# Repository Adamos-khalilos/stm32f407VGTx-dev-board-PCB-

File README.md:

# STM32F407VGTx Dev Board

A custom STM32F407VGTx development board featuring USB-C power/data, a microSD card slot, SWD debugging, a wake-up button, RGB status LEDs, and a clean regulated power supply. Designed entirely in KiCad.

<!-- Replace with your 3D render or PCB photo -->

## Features

- **MCU**: STM32F407VGTx (ARM Cortex-M4, up to 168 MHz)
- **USB**: USB-C receptacle (USB 2.0) with ESD protection (USBLC6-2P6) and BOOT0 select button
- **Power**: 5V → 3.3V regulation via LP5907MFX-3.3 LDO, decoupled with a full capacitor array on VDD/VDDA
- **Storage**: microSD card socket with dedicated pull-ups on DAT0–3/CMD/CLK and card-detect pins
- **Debug**: SWD header (Tag-Connect TC2030-NL footprint) — SWDIO, SWCLK, nRST, VCC, GND
- **Reset circuit**: Dedicated reset button with debounce and PWR_FLAG supervision
- **Wake-up circuit**: Dedicated WKUP button on a pull-down
- **Clock**: 8 MHz external crystal (HSE) with 27pF load capacitors
- **Status LEDs**: RED, GREEN, BLUE, ORANGE user LEDs (330 Ω current-limiting resistors)
- **Expansion**: Two 2×25 GPIO headers (J4 "right side", J5 "left side") breaking out nearly all MCU pins, plus 3V3/5V/GND rails

## Power Architecture

| Stage | Description |
|-------|-------------|
| USB-C VBUS (5V) | Main input power from USB-C connector (J1) |
| LP5907MFX-3.3 (U2) | Linear regulator, 5V → 3.3V |
| VDD / VDDA decoupling | Array of 100 nF capacitors + bulk 4.7 µF on the MCU supply rails |
| High-frequency filtering | Ferrite bead (FB1) + local 100 pF / 4.7 µF caps close to VREF/VDDA for clean ADC reference |

## USB-C Interface (J1)

- USB 2.0 receptacle, D+/D− routed to PA11/PA12
- ESD protection via USBLC6-2P6 (U1)
- BOOT0 select button (SW1) with pull resistors for entering system bootloader mode

## microSD Card Interface (J2)

| Signal | Description |
|--------|-------------|
| DAT0–DAT3 | SDIO data lines (10 kΩ pull-ups) |
| CLK (SDIO_CLK) | SDIO clock |
| CMD (SDIO_CMD) | SDIO command line (10 kΩ pull-up) |
| SD_DETECT / DET_A / DET_B | Card presence detection |
| SHIELD (SH) | Connector shield, tied to GND |

## SWD Debug Header (J3 — Tag-Connect TC2030-NL)

| Signal | Description |
|--------|-------------|
| VCC | +3V3 |
| SWDIO | Serial wire data |
| SWCLK | Serial wire clock |
| nRST | Reset |
| GND | Ground |

## Reset Circuit

Push-button reset with RC debounce, PWR_FLAG supervision, and a jumper (JP2) for optional external reset control.

## Wake-Up Circuit

Dedicated button (SW2) on the WKUP pin, pulled down through a 10 kΩ resistor.

## User LEDs

| LED | Color | Driver Resistor |
|-----|-------|------------------|
| D2 | Red | R9 (330 Ω) |
| D3 | Green | R10 (330 Ω) |
| D4 | Blue | R8 (330 Ω) |
| D5 | Orange | R11 (330 Ω) |

## Clock

8 MHz crystal (Y1) on HSE, with 27 pF load capacitors (C2, C3).

## GPIO Expansion Headers (J4 / J5)

Two 2×25 (50-pin) headers break out the majority of the STM32F407's GPIO ports (PA, PB, PC, PD, PE), along with GND, +3V3 and +5V rails on both headers for powering external modules.

> For the exact pin-by-pin mapping, refer to `stm32.kicad_sch` (sheet "Connector Headers") or export a netlist/pin table from KiCad — this avoids transcription errors from a schematic screenshot.

## Repository Structure
.
├── stm32.kicad_pro # KiCad project file
├── stm32.kicad_sch # Schematic
├── stm32.kicad_pcb # PCB layout
├── fp-lib-table # Footprint library table
├── Library.pretty/ # Local custom footprints
└── README.md

## Getting Started

1. Clone this repository
2. Open `stm32.kicad_pro` in [KiCad](https://www.kicad.org/) (v7 or later recommended)
3. Review the schematic (`stm32.kicad_sch`) and PCB layout (`stm32.kicad_pcb`)
4. Run DRC (Design Rules Check) before ordering fabrication
5. Generate Gerbers / fabrication files when ready to manufacture

## License

This project is licensed under the MIT License — see [LICENSE](LICENSE) for details.

## Author

Designed by **Khalil Adem**

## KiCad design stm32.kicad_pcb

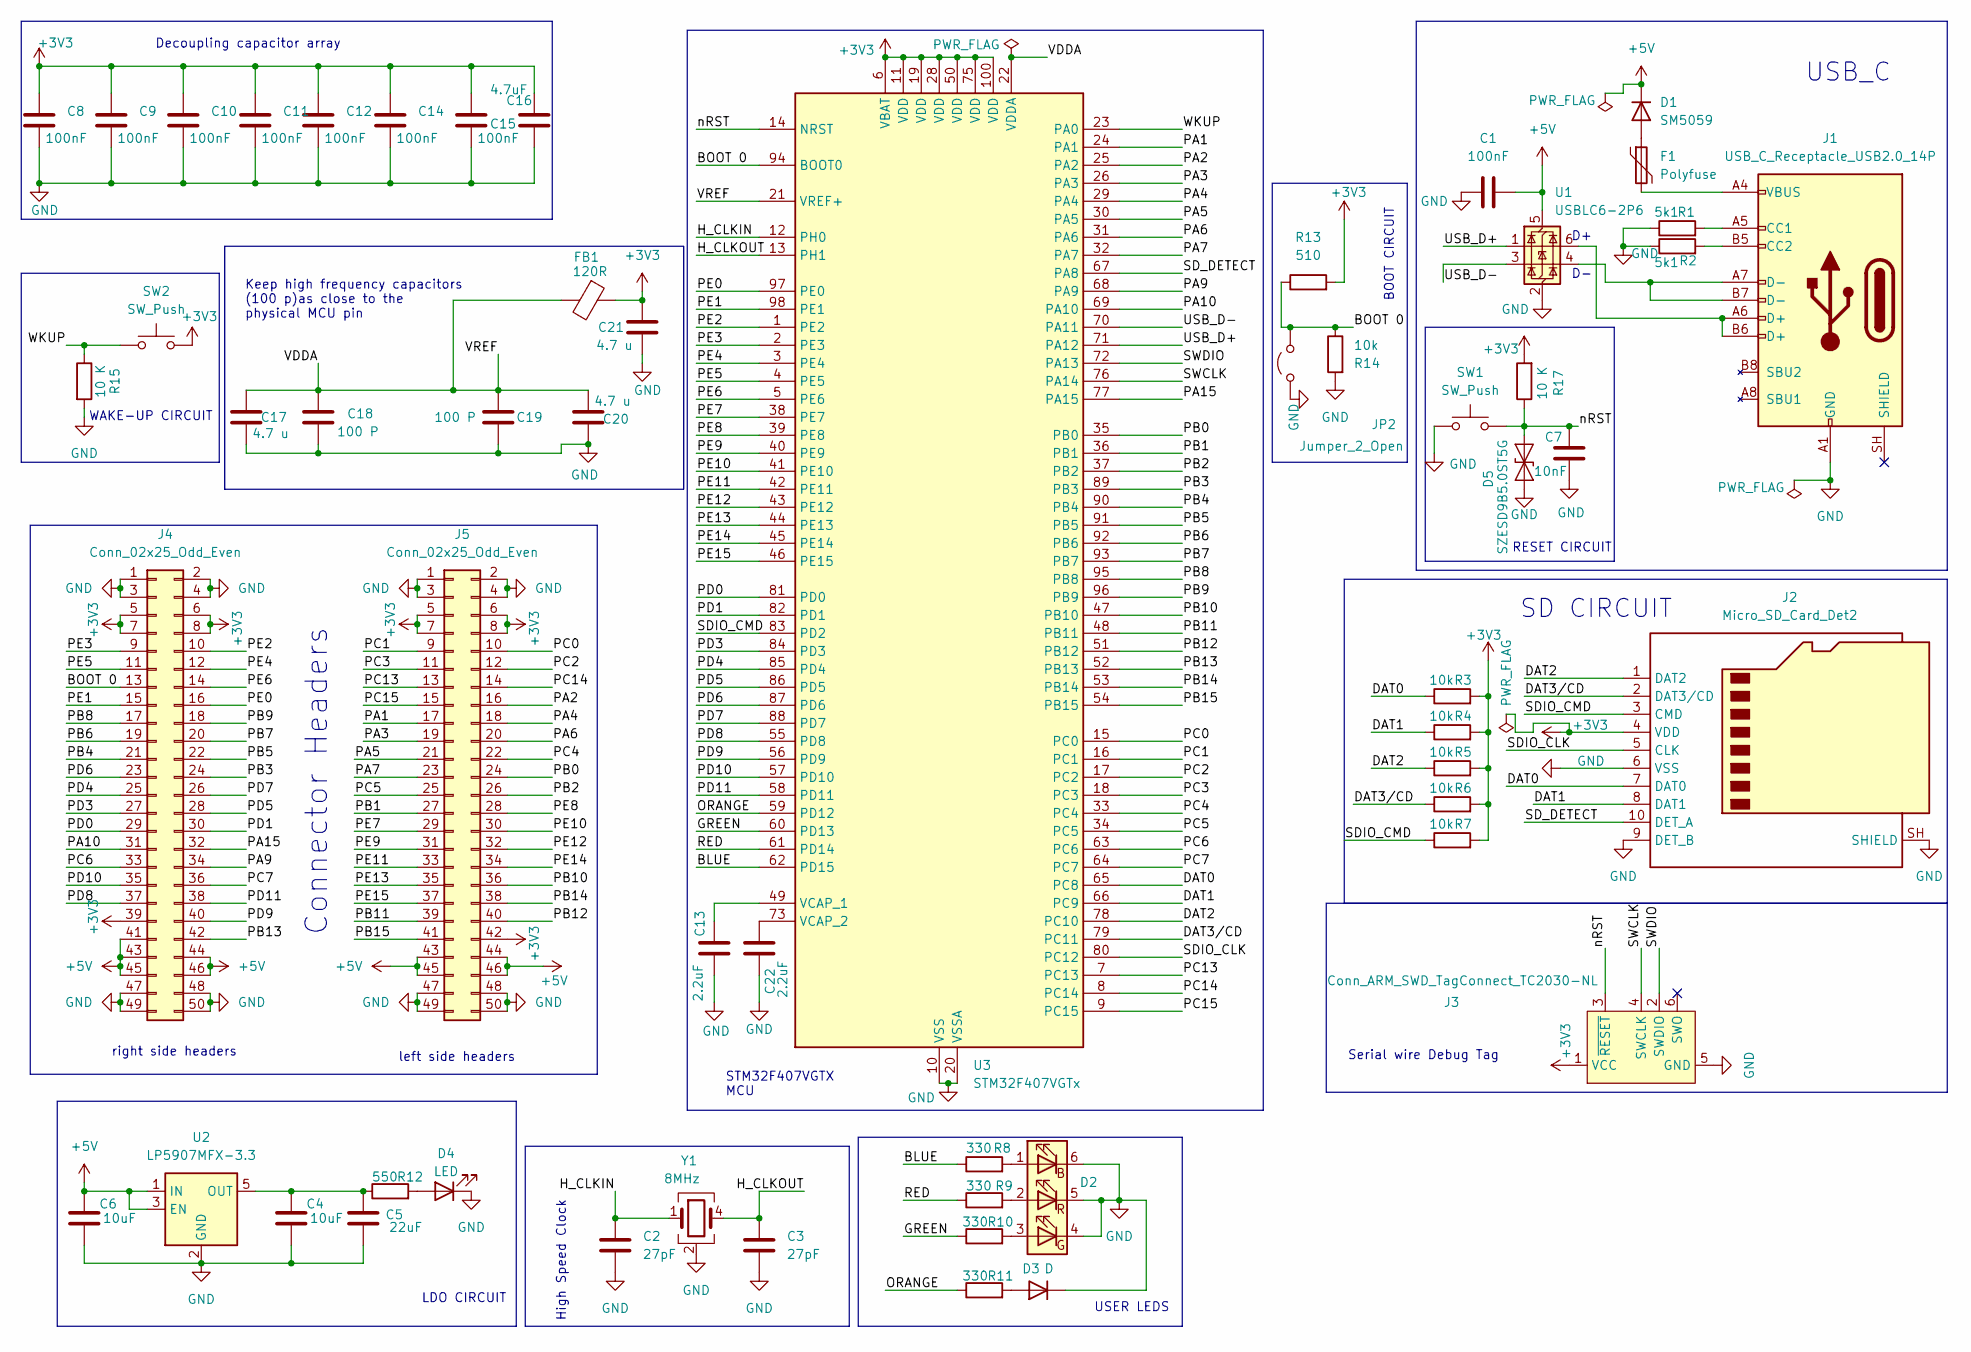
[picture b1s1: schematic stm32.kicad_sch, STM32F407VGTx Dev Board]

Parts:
C1, C8, C9, C10, C11, C12, C14, C15: 100nF; C_0603_1608Metric
C2, C3: 27pF; C_0603_1608Metric
C4, C6: 10uF; C_0805_2012Metric
C5: 22uF; C_0805_2012Metric
C7: 10nF; C_0603_1608Metric
C13, C22: 2.2uF; C_0603_1608Metric
C16: 4.7uF; C_0805_2012Metric
C17, C20, C21: 4.7 u; C_0805_2012Metric
C18, C19: 100 P; C_0603_1608Metric
D1: SM5059; D_SOD-923
D2: SMLVN6RGB; LED_ROHM_SMLVN6
D3: D; LED_0603_1608Metric
D4: LED; LED_0603_1608Metric
D5: SZESD9B5.0ST5G; D_SOD-923
F1: Polyfuse; Fuse_1206_3216Metric
FB1: 120R; L_0603_1608Metric
J1: USB_C_Receptacle_USB2.0_14P; USB_C_Receptacle_GCT_USB4105-xx-A_16P_TopMnt_Horizontal
J2: Micro_SD_Card_Det2; microSD_HC_Hirose_DM3AT-SF-PEJM5
J3: Conn_ARM_SWD_TagConnect_TC2030-NL; Tag-Connect_TC2030-IDC-NL_2x03_P1.27mm_Vertical
J4, J5: Conn_02x25_Odd_Even; PinHeader_2x25_P2.54mm_Vertical
JP2: Jumper_2_Open; SolderJumper-2_P1.3mm_Open_TrianglePad1.0x1.5mm
R1, R2: 5k1; R_0603_1608Metric
R3, R4, R5, R6, R7, R14: 10k; R_0603_1608Metric
R8, R9, R10, R11: 330; R_0603_1608Metric
R12: 550; R_0603_1608Metric
R13: 510; R_0603_1608Metric
R15, R17: 10 K; R_0603_1608Metric
SW1, SW2: SW_Push; SW_SPST_B3U-1000P
U1: USBLC6-2P6; SOT-23-6
U2: LP5907MFX-3.3; SOT-23-5
U3: STM32F407VGTx; LQFP-100_14x14mm_P0.5mm
Y1: 8MHz; Crystal_HC49-4H_Vertical

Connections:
+3V3: C8.1, C9.1, C10.1, C11.1, C12.1, C14.1, C15.1, C16.1, C21.1, FB1.1, J2.4 (VDD), J3.1 (VCC), J4.5, J4.6, J4.7, J4.8, J4.39, J5.5, J5.6, J5.7, J5.8, J5.42, R3.2, R4.2, R5.2, R6.2, R7.2, R13.2, R17.2, SW2.2, U3.6 (VBAT), U3.11 (VDD), U3.19 (VDD), U3.28 (VDD), U3.50 (VDD), U3.75 (VDD), U3.100 (VDD)
+5V: C1.2, C6.1, D1.1 (K), J4.41, J4.43, J4.44, J4.45, J4.46, J5.43, J5.44, J5.45, J5.46, U1.5 (VBUS), U2.1 (IN), U2.3 (EN)
/BLUE: R8.1, U3.62 (PD15)
/BOOT 0: J4.13, JP2.2 (B), R13.1, R14.1, U3.94 (BOOT0)
/DAT0: J2.7 (DAT0), R3.1, U3.65 (PC8)
/DAT1: J2.8 (DAT1), R4.1, U3.66 (PC9)
/DAT2: J2.1 (DAT2), R5.1, U3.78 (PC10)
/DAT3/CD: J2.2 (DAT3/CD), R6.1, U3.79 (PC11)
/GREEN: R10.1, U3.60 (PD13)
/H_CLKIN: C2.1, U3.12 (PH0), Y1.1
/H_CLKOUT: C3.1, U3.13 (PH1), Y1.4
/ORANGE: R11.1, U3.59 (PD12)
/PA1: J5.17, U3.24 (PA1)
/PA2: J5.16, U3.25 (PA2)
/PA3: J5.19, U3.26 (PA3)
/PA4: J5.18, U3.29 (PA4)
/PA5: J5.21, U3.30 (PA5)
/PA6: J5.20, U3.31 (PA6)
/PA7: J5.23, U3.32 (PA7)
/PA9: J4.34, U3.68 (PA9)
/PA10: J4.31, U3.69 (PA10)
/PA15: J4.32, U3.77 (PA15)
/PB0: J5.24, U3.35 (PB0)
/PB1: J5.27, U3.36 (PB1)
/PB2: J5.26, U3.37 (PB2)
/PB3: J4.24, U3.89 (PB3)
/PB4: J4.21, U3.90 (PB4)
/PB5: J4.22, U3.91 (PB5)
/PB6: J4.19, U3.92 (PB6)
/PB7: J4.20, U3.93 (PB7)
/PB8: J4.17, U3.95 (PB8)
/PB9: J4.18, U3.96 (PB9)
/PB10: J5.36, U3.47 (PB10)
/PB11: J5.39, U3.48 (PB11)
/PB12: J5.40, U3.51 (PB12)
/PB13: J4.42, U3.52 (PB13)
/PB14: J5.38, U3.53 (PB14)
/PB15: J5.41, U3.54 (PB15)
/PC0: J5.10, U3.15 (PC0)
/PC1: J5.9, U3.16 (PC1)
/PC2: J5.12, U3.17 (PC2)
/PC3: J5.11, U3.18 (PC3)
/PC4: J5.22, U3.33 (PC4)
/PC5: J5.25, U3.34 (PC5)
/PC6: J4.33, U3.63 (PC6)
/PC7: J4.36, U3.64 (PC7)
/PC13: J5.13, U3.7 (PC13)
/PC14: J5.14, U3.8 (PC14)
/PC15: J5.15, U3.9 (PC15)
/PD0: J4.29, U3.81 (PD0)
/PD1: J4.30, U3.82 (PD1)
/PD3: J4.27, U3.84 (PD3)
/PD4: J4.25, U3.85 (PD4)
/PD5: J4.28, U3.86 (PD5)
/PD6: J4.23, U3.87 (PD6)
/PD7: J4.26, U3.88 (PD7)
/PD8: J4.37, U3.55 (PD8)
/PD9: J4.40, U3.56 (PD9)
/PD10: J4.35, U3.57 (PD10)
/PD11: J4.38, U3.58 (PD11)
/PE0: J4.16, U3.97 (PE0)
/PE1: J4.15, U3.98 (PE1)
/PE2: J4.10, U3.1 (PE2)
/PE3: J4.9, U3.2 (PE3)
/PE4: J4.12, U3.3 (PE4)
/PE5: J4.11, U3.4 (PE5)
/PE6: J4.14, U3.5 (PE6)
/PE7: J5.29, U3.38 (PE7)
/PE8: J5.28, U3.39 (PE8)
/PE9: J5.31, U3.40 (PE9)
/PE10: J5.30, U3.41 (PE10)
/PE11: J5.33, U3.42 (PE11)
/PE12: J5.32, U3.43 (PE12)
/PE13: J5.35, U3.44 (PE13)
/PE14: J5.34, U3.45 (PE14)
/PE15: J5.37, U3.46 (PE15)
/RED: R9.1, U3.61 (PD14)
/SDIO_CLK: J2.5 (CLK), U3.80 (PC12)
/SDIO_CMD: J2.3 (CMD), R7.1, U3.83 (PD2)
/SD_DETECT: J2.10 (DET_A), U3.67 (PA8)
/SWCLK: J3.4 (SWCLK), U3.76 (PA14)
/SWDIO: J3.2 (SWDIO), U3.72 (PA13)
/USB_D+: U1.1 (I/O1), U3.71 (PA12)
/USB_D-: U1.3 (I/O2), U3.70 (PA11)
/VDDA: C17.1, C18.1, C19.1, C20.1, FB1.2, U3.21 (VREF+), U3.22 (VDDA)
/WKUP: R15.1, SW2.1, U3.23 (PA0)
/nRST: C7.1, D5.2 (A2), J3.3 (~RESET), R17.1, SW1.2, U3.14 (NRST)
GND: C1.1, C2.2, C3.2, C4.2, C5.2, C6.2, C7.2, C8.2, C9.2, C10.2, C11.2, C12.2, C13.2, C14.2, C15.2, C16.2, C17.2, C18.2, C19.2, C20.2, C21.2, C22.2, D2.4 (GK), D2.5 (RK), D2.6 (BK), D3.1 (K), D4.1 (K), D5.1 (A1), J1.A1 (GND), J1.A12 (GND), J1.B1 (GND), J1.B12 (GND), J2.6 (VSS), J2.9 (DET_B), J2.SH (SHIELD), J3.5 (GND), J4.1, J4.2, J4.3, J4.4, J4.47, J4.48, J4.49, J4.50, J5.1, J5.2, J5.3, J5.4, J5.47, J5.48, J5.49, J5.50, JP2.1 (A), R1.1, R2.1, R14.2, R15.2, SW1.1, U1.2 (GND), U2.2 (GND), U3.10 (VSS), U3.20 (VSSA), U3.27 (VSS), U3.74 (VSS), U3.99 (VSS), Y1.2 (G), Y1.3 (G)
unnamed: D1.2 (A), F1.1
unnamed: D2.1 (BA), R8.2
unnamed: D2.3 (GA), R10.2
unnamed: D2.2 (RA), R9.2
unnamed: D3.2 (A), R11.2
unnamed: D4.2 (A), R12.2
unnamed: F1.2, J1.A4 (VBUS), J1.A9 (VBUS), J1.B4 (VBUS), J1.B9 (VBUS)
unnamed: J1.A5 (CC1), R1.2
unnamed: J1.B5 (CC2), R2.2
unnamed: J1.A6 (D+), J1.B6 (D+), U1.6 (I/O1)
unnamed: J1.A7 (D-), J1.B7 (D-), U1.4 (I/O2)
unnamed: C4.1, C5.1, R12.1, U2.5 (OUT)
unnamed: C13.1, U3.49 (VCAP_1)
unnamed: C22.1, U3.73 (VCAP_2)

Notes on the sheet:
STM32F407VGTX MCU
WAKE-UP CIRCUIT
High Speed Clock
Keep high frequency capacitors (100 p)as close to the physical MCU pin
LDO CIRCUIT
SD CIRCUIT
USB_C
Decoupling capacitor array
left side headers
USER LEDS
RESET CIRCUIT
Connector Headers
right side headers
Serial wire Debug Tag
BOOT CIRCUIT

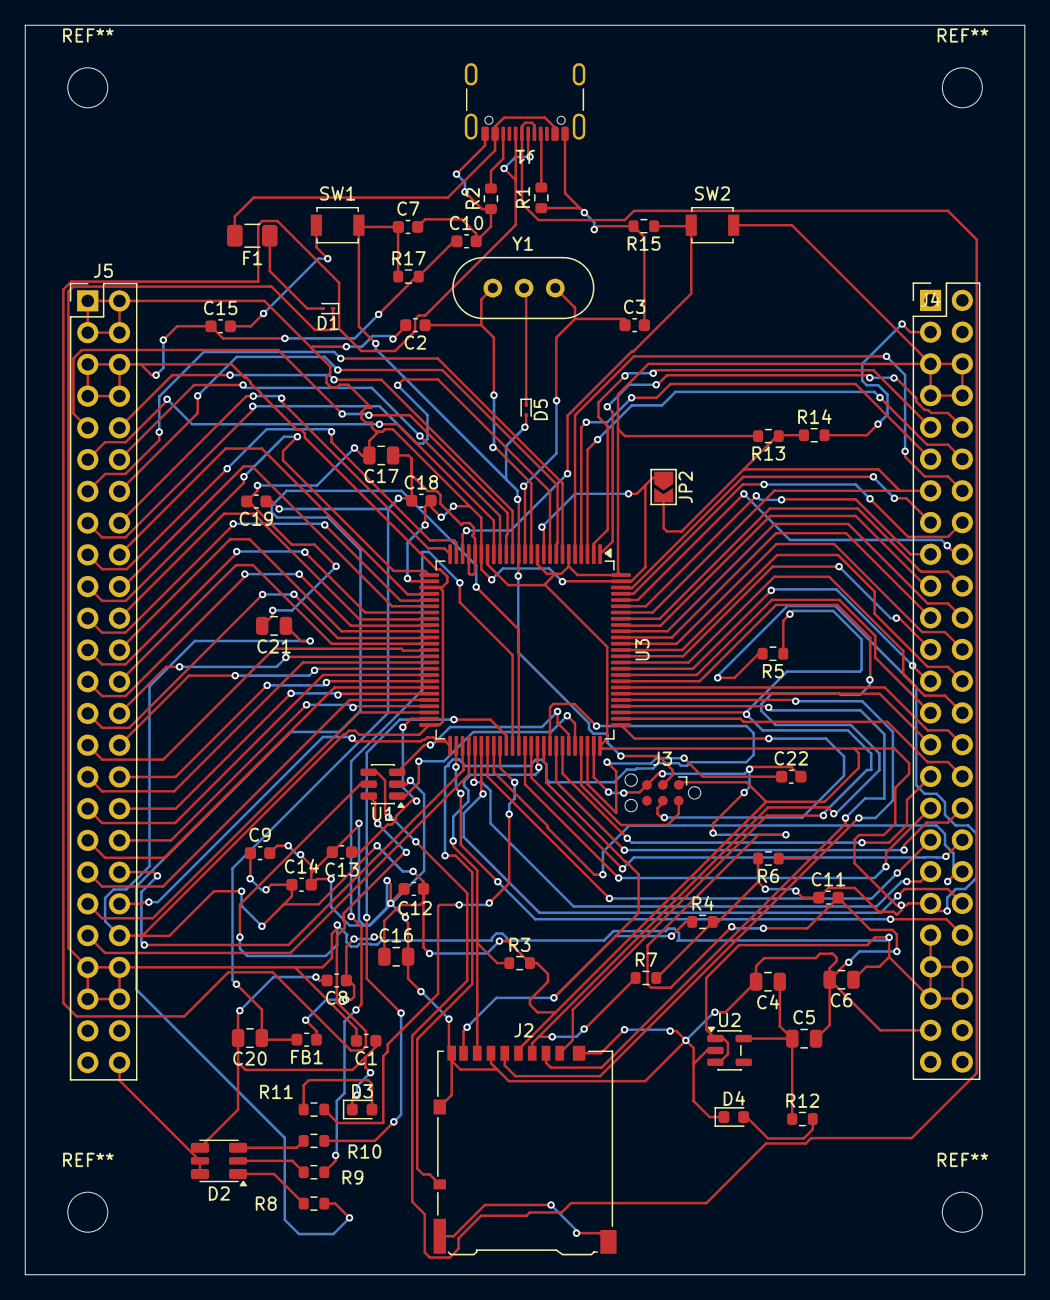
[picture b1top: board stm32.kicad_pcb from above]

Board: 2 copper layers, 80.0 x 100.0 mm, 57 parts (0 on the bottom side), 102 nets.
